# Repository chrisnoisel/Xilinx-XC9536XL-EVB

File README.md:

# Xilinx_XC9536XL_EVB
Slightly modified startingelectronics.org's Xilinx CPLD board (http://startingelectronics.org/projects/xilinx-CPLD-board/)

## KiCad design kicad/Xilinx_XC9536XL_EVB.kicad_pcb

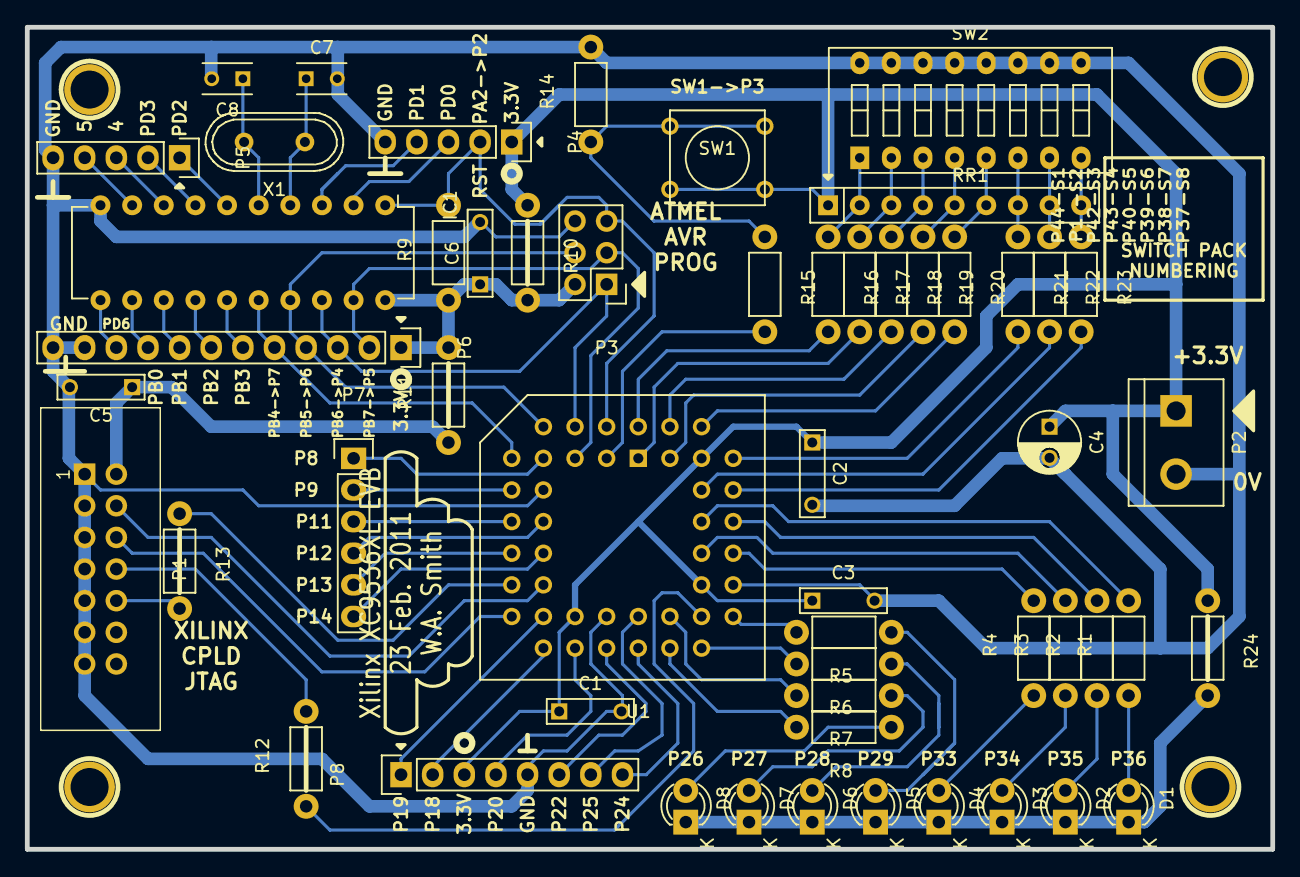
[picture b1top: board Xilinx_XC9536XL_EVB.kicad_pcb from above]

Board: 2 copper layers, 100.0 x 66.0 mm, 58 parts (0 on the bottom side), 75 nets.

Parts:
1PIN, 1PIN#2, 1PIN#3, 1PIN#4: P***; 1pin
C1, C2, C3, C5, C6: 100n; C_Rect_L7_W2_P5
C4: 10uF; C_Radial_D5_L6_P2.5
C7, C8: 22p; C_Rect_L4_W2.5_P2.5
D1, D2, D3, D4, D5, D6, D7, D8: LED; LED-3MM
IC1: ATTINY2313-P; DIP-20_W7.62mm
P1: CONN_7X2; IDC_Header_Straight_14pins
P2: CONN_2; bornier2
P3: CONN_3X2; Pin_Header_Straight_2x03
P4, P5: CONN_5; Pin_Header_Straight_1x05
P6: CONN_12; Pin_Header_Straight_1x12
P7: CONN_6; Pin_Header_Straight_1x06
P8: CONN_8; Pin_Header_Straight_1x08
R1, R2, R3, R4, R5, R6, R7, R8: 330R; Resistor_Horizontal_RM7mm
R9: 10k; Resistor_Horizontal_RM7mm
R10, R11, R12, R13, R24: 0R; Resistor_Horizontal_RM7mm
R14, R15, R16, R17, R18, R19, R20, R21, R22, R23: 4k7; Resistor_Horizontal_RM7mm
RR1: 4k7; Resistor_Array_SIP9
SW1: SW_PUSH; SW_PUSH_SMALL
SW2: SW_DIP_8; SW_DIP_x8_Slide
U1: XC9536XLPC44; PLCC44
X1: XTAL; Crystal_HC49-U_Vertical

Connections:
+3.3V: C1.1, C2.1, C3.1, C4.1, P2.1, P4.1, P8.3, R10.1, R24.1, RR1.1, SW1.2, U1.21, U1.32, U1.41
/3V3P: C6.1, IC1.20, P3.2, P6.1, R9.1, R10.2, R11.2
/L1: R1.2, U1.36
/L2: R2.2, U1.35
/L3: R3.2, U1.34
/L4: R4.2, U1.33
/L5: R5.2, U1.29
/L6: R6.2, U1.28
/L7: R7.2, U1.27
/L8: R8.2, U1.26
/MISO: IC1.18, P3.1, P6.3, U1.4
/MOSI: IC1.17, P3.4, P6.4, U1.6
/O1: P8.1, U1.19
/O2: P8.2, U1.18
/O3: P8.4, U1.20
/O4: P8.6, U1.22
/O5: P8.7, U1.25
/O6: P8.8, U1.24
/PD6: IC1.11, P6.10
/RESET: IC1.1, P3.5, P4.2, R9.2, U1.2
/S1: R16.2, U1.44
/S2: R17.2, U1.1
/S3: R18.2, U1.42
/S4: R19.2, U1.43
/S5: R20.2, U1.40
/S6: R21.2, U1.39
/S7: R22.2, U1.38
/S8: R23.2, U1.37
/SCK: IC1.19, P3.3, P6.2, U1.5
/TCK: P1.6, U1.17
/TDI: R13.1, U1.15
/TDO: R12.1, U1.30
/TMS: P1.4, U1.16
GND: C1.2, C2.2, C3.2, C4.2, C5.2, C6.2, C7.2, C8.2, IC1.10, P1.1, P1.3, P1.5, P1.7, P1.9, P1.11, P1.13, P2.2, P3.6, P4.5, P5.5, P6.11, P6.12, P8.5, R14.2, SW2.9, SW2.10, SW2.11, SW2.12, SW2.13, SW2.14, SW2.15, SW2.16, U1.10, U1.23, U1.31
unnamed: C5.1, P1.2, R11.1
unnamed: C7.1, IC1.4, X1.1
unnamed: C8.1, IC1.5, X1.2
unnamed: D1.1, D2.1, D3.1, D4.1, D5.1, D6.1, D7.1, D8.1, R24.2
unnamed: D1.2, R1.1
unnamed: D2.2, R2.1
unnamed: D3.2, R3.1
unnamed: D4.2, R4.1
unnamed: D5.2, R5.1
unnamed: D6.2, R6.1
unnamed: D7.2, R7.1
unnamed: D8.2, R8.1
unnamed: IC1.2, P4.3
unnamed: IC1.3, P4.4
unnamed: IC1.6, P5.1
unnamed: IC1.7, P5.2
unnamed: IC1.8, P5.3
unnamed: IC1.9, P5.4
unnamed: IC1.12, P6.9
unnamed: IC1.13, P6.8
unnamed: IC1.14, P6.7
unnamed: IC1.15, P6.6
unnamed: IC1.16, P6.5, U1.7
unnamed: P1.8, R12.2
unnamed: P1.10, R13.2
unnamed: P7.1, U1.8
unnamed: P7.2, U1.9
unnamed: P7.3, U1.11
unnamed: P7.4, U1.12
unnamed: P7.5, U1.13
unnamed: P7.6, U1.14
unnamed: R14.1, R15.1, SW1.1
unnamed: R15.2, U1.3
unnamed: R16.1, RR1.2, SW2.1
unnamed: R17.1, RR1.3, SW2.2
unnamed: R18.1, RR1.4, SW2.3
unnamed: R19.1, RR1.5, SW2.4
unnamed: R20.1, RR1.6, SW2.5
unnamed: R21.1, RR1.7, SW2.6
unnamed: R22.1, RR1.8, SW2.7
unnamed: R23.1, RR1.9, SW2.8

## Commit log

2015-11-19 original board source
2015-12-06 updated footprints libraries (pull-request to official git pending)
2015-12-07 updated pcb with new footprints + removed old files
2015-12-07 more file cleanup
2015-12-08 even more clean up
2015-12-08 added 3.3v linear regulator
2016-01-02 added some space between linear regulator and mounting screw
2016-01-04 added footprint libraries as submodules for flexibility
2016-02-01 switched to official footprint git repos since PRs have been accepted.
2016-12-27 cleanup + better gitignore
2016-12-27 updated with new libraries/footprints
2016-12-27 updated pcb with new footprints
2016-12-27 pcb updated with new footprints
2018-11-24 automatic switch to kicad 5 format
